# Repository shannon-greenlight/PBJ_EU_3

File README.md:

# The PBJ EU
The PBJ EU is a hardware development system for Eurorack synthesizers

Features:
- 800 point solderless proto board
- 4 switched 3.5mm jacks.
- Tip and Switch signals are routed from the jacks to the wiring connector.
- +/- 12V and adjustable A and B power rails are routed to the wiring connector.
- LED monitors for each jack. Red indicates positive voltage. Green indicates negative.
- 2 Test points per jack gives convenient access for probing and injecting signals.
- 2 Large Ground connection points are excellent for attaching alligator clips.
- 3 MULT switches connect jack 1 to 2, jack 2 to 3 or jack 3 to 4.
- Power is switched.
- Power indicators show the status of all power rails.
- 22 HP wide.
- Ready when you are. Everything you need with no pre-setup required!

# Making Changes
The process of making changes usually starts with altering the schematic followed by other actions as required.
This requires a properly configured KiCAD installation. Download the KiCAD [repo](https://github.com/shannon-greenlight/KiCAD) and follow the instructions in the README to install.
When the system is configured follow the steps outlined below. Some steps are optional depending on what has changed.

These procedures have been optimized for use with Digi-Key and JLCPCB. They should be a good starting point for use with other vendors.

- Update schematic
	- Update revision in File->Page Settings
	- Plot pdf version of schematic.
- If any parts have changed, Update BOMs
	- From KiCAD Schematic Editor, run Tools->Generate Legacy Bill of Materials using bom2grouped_csv.xsl
		- bom2grouped_csv.xsl is found in the Greenface KiCAD repo.
		- Here is a sample command line: xsltproc -o "%O.csv" "C:\Users\shann\Dropbox\KiCAD\bom2grouped_csv.xsl" "%I"
		- This creates a .csv and an xml file. The xml file is used in the next step.
	- Run _combine_boms.bat_
		- This creates the following .csv files
			- BOM\Digi-Key\PBJ_EU_combined.csv (all components, both boards combined)
			- BOM\Digi-Key\PBJ_EU_full.csv (all components, top board)
			- BOM\Digi-Key\PBJ_EU_split.csv (just components on top board that are not found in LCSC BOM)
			- BOM\LCSC\PBJ_EU_bom.csv (just components on top board to be assembled by JLCPCB)
			- sub\BOM\Digi-Key\PBJ_EU_full.csv (all components, sub board)
			- sub\BOM\Digi-Key\PBJ_EU_split.csv (just components on sub board that are not found in LCSC BOM)
			- sub\BOM\LCSC\PBJ_EU_bom.csv (just components on sub board to be assembled by JLCPCB)
		- combine_boms.bat requires Python and the Greenface Python [libraries](https://github.com/shannon-greenlight/PYTHON_BOM) to be installed
			- Place the Greenface Python folder in a convienient place on your computer and set the variable %plugin_dir% to point to that folder location.
			- Python is invoked as 'py' in the batch file. This may need to be changed depending on your Python installation.
- Update layout if required
	- Update revision in File->Page Settings
	- Plot the Gerber files
		- Set the output directory to _fab\gerber\\_
		- Make sure to Generate Drill Files
		- Create a zip archive of the Gerber files. (This is required by JLCPCB)
			- Use Windows Send To Compressed Folder. Rename the resulting file to PBJ_EU_gerbers.zip
			- Alternatively, use zip_gerbers.bat
			- zip_gerbers.bat requires 7z.exe
			- Edit this file if 7z.exe is installed somewhere other than C:\Program Files\7-Zip
	- Create the pick-and-place files
		- From KiCAD PCB Editor, run File->Fabrication Outputs->Component Placement
		- Set the output directory to _fab\pos\\_
		- This creates the files used by the next step
		- Update PBJ_EU_cpl.xlsx
			- PBJ_EU_cpl.xlsx uses Excel Queries to convert pos\PBJ_EU-top-pos.csv into a format compatible with JLCPCB
			- Excel requires an absolute path to the source folder of the data. Edit the query to enter the path to your project.
			- *note: This process does not produce a perfect placement file due to differences in how KiCAD and JLCPCB orient components. However, JLCPCB is able to use the file without problems. So, even if the placement looks wrong when specifying the build, they will use the file and produce correct boards.
			- **note: There is probably a KiCAD plugin available that does a better job. The user is encouraged to try this route and report the results back.
- Upload to JLCPCB
	- JLCPCB requires the following files:
		- fab\PBJ_EU_gerbers.zip
		- fab\PBJ_EU_cpl.xlsx (only needed for assembly)
		- bom\LCSC\PBJ_EU_bom.csv (only needed for assembly)

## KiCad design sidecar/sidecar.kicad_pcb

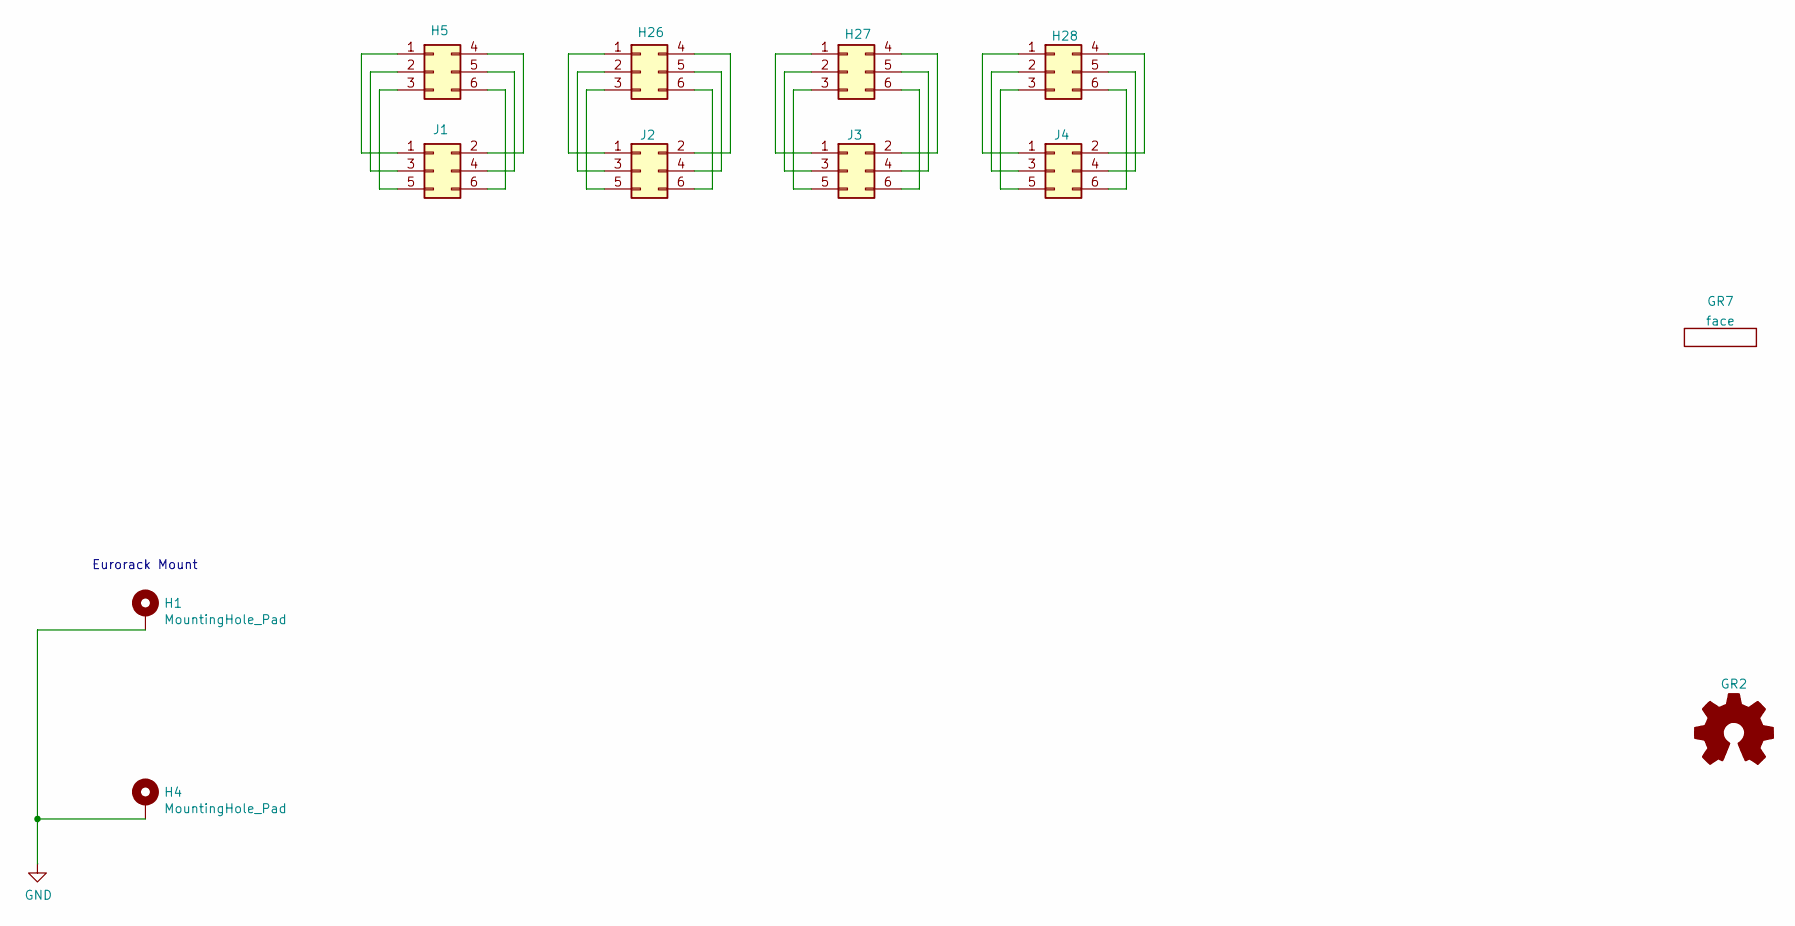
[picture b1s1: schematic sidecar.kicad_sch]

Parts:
GR2: Logo_Open_Hardware_Small; OSHW-Logo_5.7x6mm_SilkScreen
GR7: face; small_face
H1, H4: MountingHole_Pad; MountingHole_3.2mm_M3_Slot
H5: Adj 1; Potentiometer_Sidecar
H26: Adj 2; Potentiometer_Sidecar
H27: Adj 3; Potentiometer_Sidecar
H28: Adj 4; Potentiometer_Sidecar
J1, J2, J3, J4: Conn_02x03_Odd_Even; PinSocket_2x03_P2.54mm_Vertical; Digi-Key Part S7071-ND

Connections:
GND: H1.1, H4.1
unnamed: H5.1, J1.1
unnamed: H5.2, J1.3
unnamed: H5.3, J1.5
unnamed: H5.4, J1.2
unnamed: H5.5, J1.4
unnamed: H5.6, J1.6
unnamed: H26.1, J2.1
unnamed: H26.2, J2.3
unnamed: H26.3, J2.5
unnamed: H26.4, J2.2
unnamed: H26.5, J2.4
unnamed: H26.6, J2.6
unnamed: H27.1, J3.1
unnamed: H27.2, J3.3
unnamed: H27.3, J3.5
unnamed: H27.4, J3.2
unnamed: H27.5, J3.4
unnamed: H27.6, J3.6
unnamed: H28.1, J4.1
unnamed: H28.2, J4.3
unnamed: H28.3, J4.5
unnamed: H28.4, J4.2
unnamed: H28.5, J4.4
unnamed: H28.6, J4.6

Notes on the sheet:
Eurorack Mount

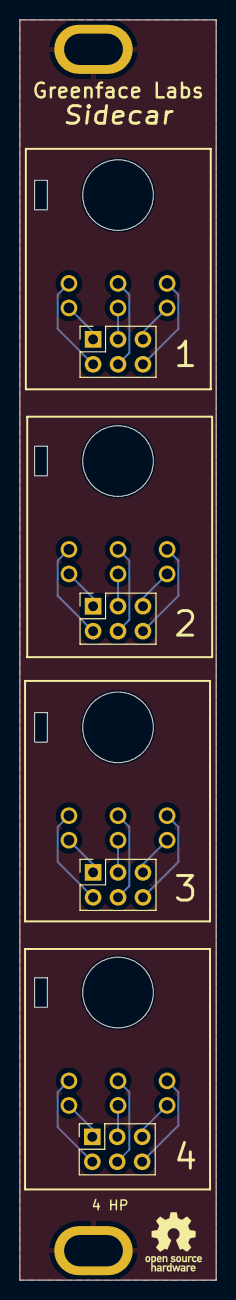
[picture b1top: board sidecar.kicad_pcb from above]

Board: 2 copper layers, 20.0 x 128.4 mm, 11 parts (0 on the bottom side), 25 nets.

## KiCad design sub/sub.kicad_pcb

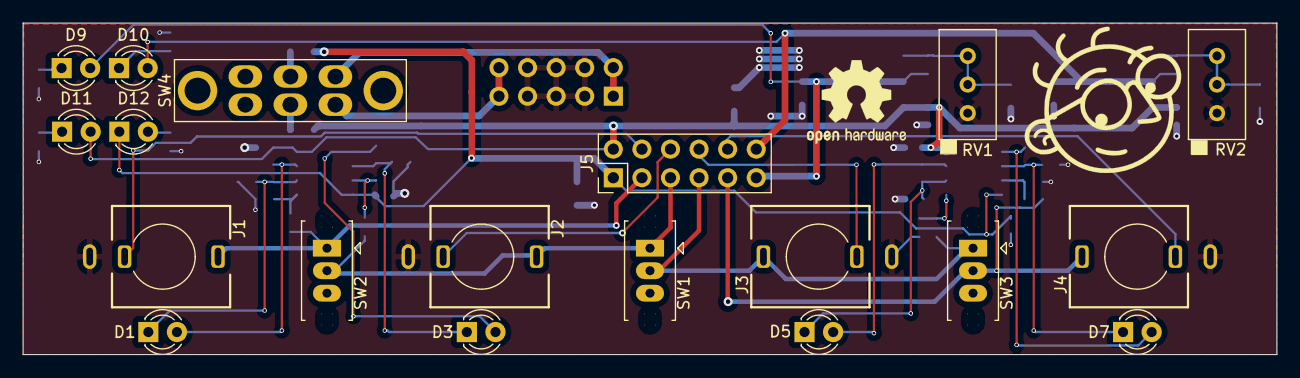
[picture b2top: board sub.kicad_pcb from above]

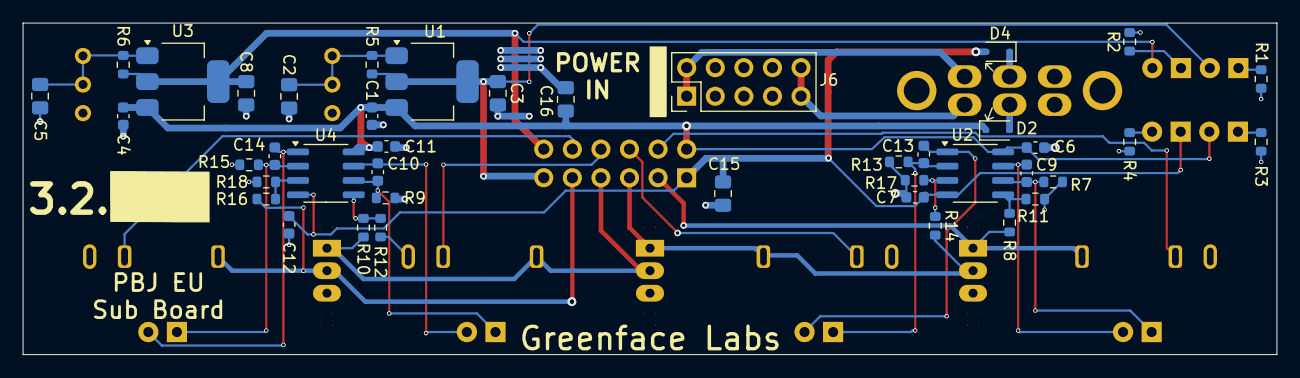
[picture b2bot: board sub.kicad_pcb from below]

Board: 2 copper layers, 111.4 x 29.4 mm, 62 parts (41 on the bottom side), 35 nets.

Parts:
C1, C4, C6, C7, C11, C12: 100nF; C_0603_1608Metric
C2, C5: 10uF; C_0805_2012Metric_Pad1.18x1.45mm_HandSolder
C3, C8, C15, C16: 22uF; C_0805_2012Metric_Pad1.18x1.45mm_HandSolder
C9, C10, C13, C14: 10nF; C_0603_1608Metric
D1, D3, D5, D7: LED_RG; LED_D3.0mm
D2, D4: 1N5819WS; D_SOD-323
D9: GREEN LED; LED_D3.0mm
D10: YELLOW LED; LED_D3.0mm
D11: RED LED; LED_D3.0mm
D12: BLUE LED; LED_D3.0mm
GR1: small_logo; small_face
GR2: OSWF_logo; OSHW-Logo2_9.8x8mm_SilkScreen
J1, J2, J3, J4: Thonk 3.5mm Jack; Jack_3.5mm_QingPu_WQP-PJ398SM_Vertical
J5: Conn_02x06_Odd_Even; PinHeader_2x06_P2.54mm_Vertical
J6: Conn_02x05_Odd_Even; PinHeader_2x05_P2.54mm_Vertical
R1, R2, R5, R6: 620; R_0603_1608Metric
R3, R4: 2.2K; R_0603_1608Metric
R7, R9, R13, R15: 510; R_0603_1608Metric
R8, R10, R11, R12, R14, R16, R17, R18: 1M; R_0603_1608Metric
RV1, RV2: 5K; Potentiometer_Bourns_3296W_Vertical
SW1, SW2, SW3: SW_SPDT; SW_Slide_EG1248
SW4: MFS201N-9-Z; MFS201N−9−Z
U1, U3: LM317; SOT-223-3_TabPin2
U2, U4: TL072CDR; SOIC-8_3.9x4.9mm_P1.27mm

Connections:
+12V: C1.1, C4.1, C6.1, C11.1, C16.2, D2.1 (K), D11.2 (A), J5.2, U1.3 (VI), U2.8 (V+), U3.3 (VI), U4.8 (V+)
-12V: C7.2, C12.2, C15.1, D4.2 (A), D12.1 (K), J5.1, U2.4 (V-), U4.4 (V-)
A Rail: C3.1, D9.2 (A), J5.11, R5.1, U1.2 (VO)
B Rail: C8.1, D10.2 (A), J5.12, R6.1, U3.2 (VO)
GND: C1.2, C2.2, C3.2, C4.2, C5.2, C6.2, C7.1, C8.2, C11.2, C12.1, C15.2, C16.1, J1.S, J2.S, J3.S, J4.S, J6.3, J6.4, J6.5, J6.6, J6.7, J6.8, R1.1, R2.2, R3.2, R4.2, R7.1, R9.1, R11.2, R12.2, R13.1, R15.1, R17.2, R18.2, RV1.1, RV2.1
unnamed: C9.2, D1.2 (AK), U2.7
unnamed: C9.1, D1.1 (KA), R7.2, U2.6 (-)
unnamed: D2.2 (A), SW4.5 (B)
unnamed: C13.2, D3.2 (AK), U2.1
unnamed: C13.1, D3.1 (KA), R13.2, U2.2 (-)
unnamed: D4.1 (K), SW4.2 (B)
unnamed: C10.2, D5.2 (AK), U4.7
unnamed: C10.1, D5.1 (KA), R9.2, U4.6 (-)
unnamed: C14.2, D7.2 (AK), U4.1
unnamed: C14.1, D7.1 (KA), R15.2, U4.2 (-)
unnamed: D9.1 (K), R1.2
unnamed: D10.1 (K), R2.1
unnamed: D11.1 (K), R3.1
unnamed: D12.2 (A), R4.1
unnamed: J6.1, J6.2, SW4.3 (C)
unnamed: J6.9, J6.10, SW4.6 (C)
unnamed: C2.1, R5.2, RV1.2, RV1.3, U1.1 (ADJ)
unnamed: R14.1, R17.1, U2.3 (+)
unnamed: R8.1, R11.1, U2.5 (+)
unnamed: C5.1, R6.2, RV2.2, RV2.3, U3.1 (ADJ)
unnamed: R16.1, R18.1, U4.3 (+)
unnamed: R10.1, R12.1, U4.5 (+)
SW1: J1.TN, J5.4
SW2: J2.TN, J5.6
SW3: J3.TN, J5.8
SW4: J4.TN, J5.10
Tip1: J1.T, J5.3, R8.2, SW2.1 (A)
Tip2: J2.T, J5.5, R14.2, SW1.1 (A), SW2.2 (B)
Tip3: J3.T, J5.7, R10.2, SW1.2 (B), SW3.1 (A)
Tip4: J4.T, J5.9, R16.2, SW3.2 (B)

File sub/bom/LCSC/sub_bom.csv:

"Designator","Comment","Footprint","JLCPCBPart#"
"C1, C4, C6, C7, C11, C12, ","100nF","Capacitor_SMD:C_0603_1608Metric","C14663"
"C2, C5, ","10uF","Capacitor_SMD:C_0805_2012Metric_Pad1.18x1.45mm_HandSolder","C15850"
"C3, C8, ","22uF","Capacitor_SMD:C_0805_2012Metric_Pad1.18x1.45mm_HandSolder","C76637"
"C9, C10, C13, C14, ","10nF","Capacitor_SMD:C_0603_1608Metric","C1589"
"J6, ","Conn_02x05_Odd_Even","Connector_PinHeader_2.54mm:PinHeader_2x05_P2.54mm_Vertical","C492422"
"R1, R2, R5, R6, ","620","Resistor_SMD:R_0603_1608Metric","C23220"
"R3, R4, ","2.2K","Resistor_SMD:R_0603_1608Metric","C4190"
"R7, R9, R13, R15, ","510","Resistor_SMD:R_0603_1608Metric","C23193"
"R8, R10, R11, R12, R14, R16, R17, R18, ","1M","Resistor_SMD:R_0603_1608Metric","C22935"
"U1, U3, ","LM317","Package_TO_SOT_SMD:SOT-223-3_TabPin2","C51466"
"U2, U4, ","TL072CDR","Package_SO:SOIC-8_3.9x4.9mm_P1.27mm","C6961"

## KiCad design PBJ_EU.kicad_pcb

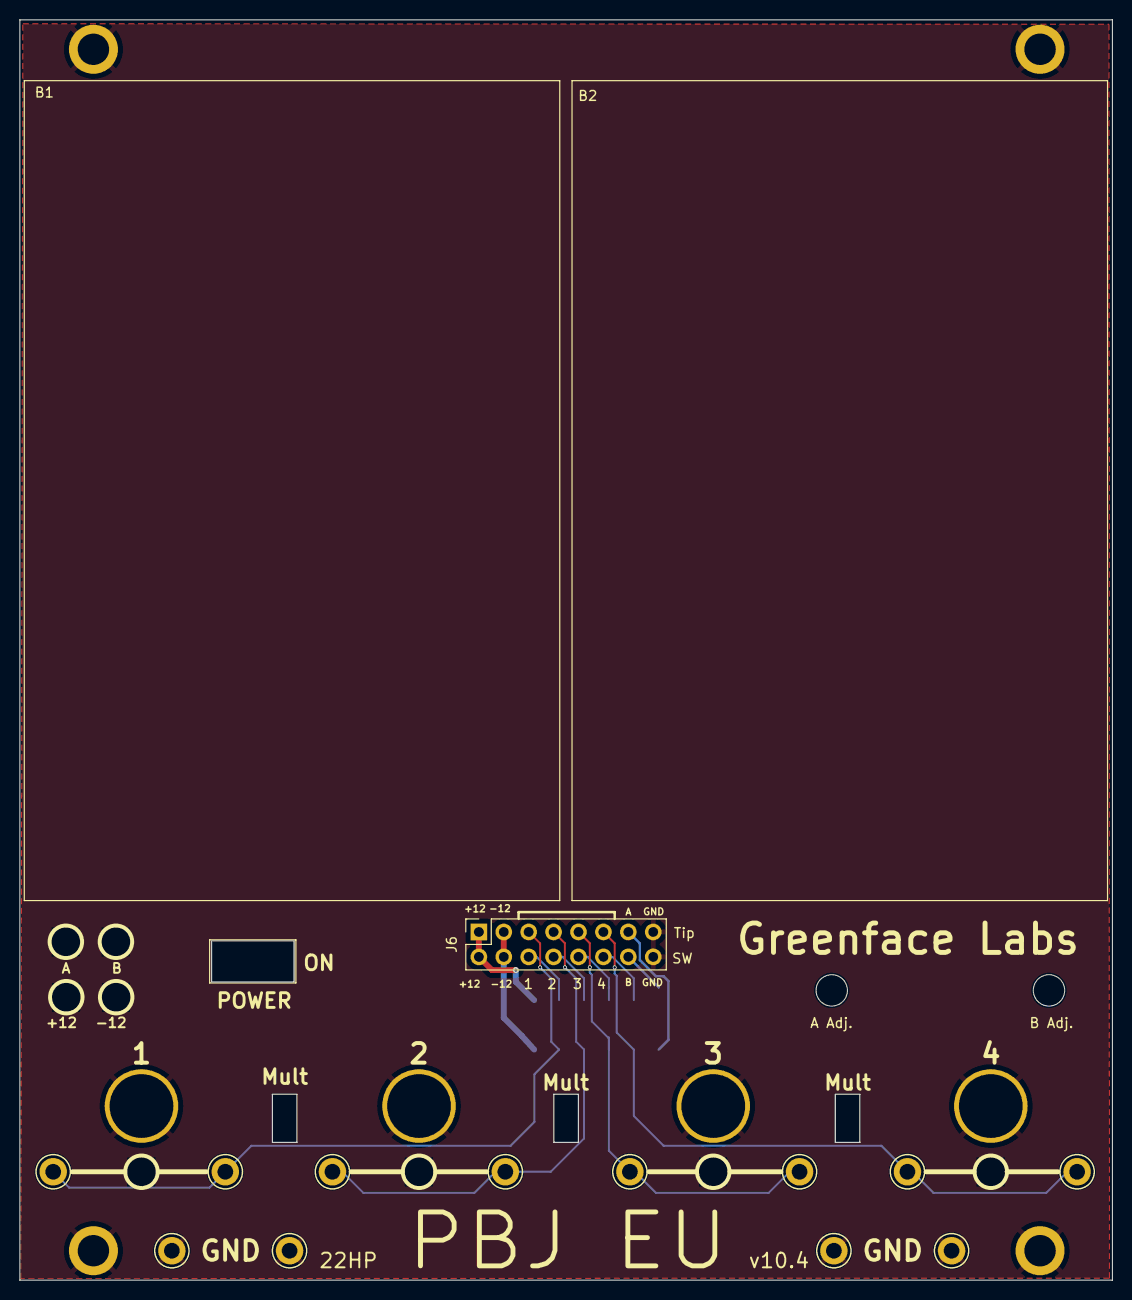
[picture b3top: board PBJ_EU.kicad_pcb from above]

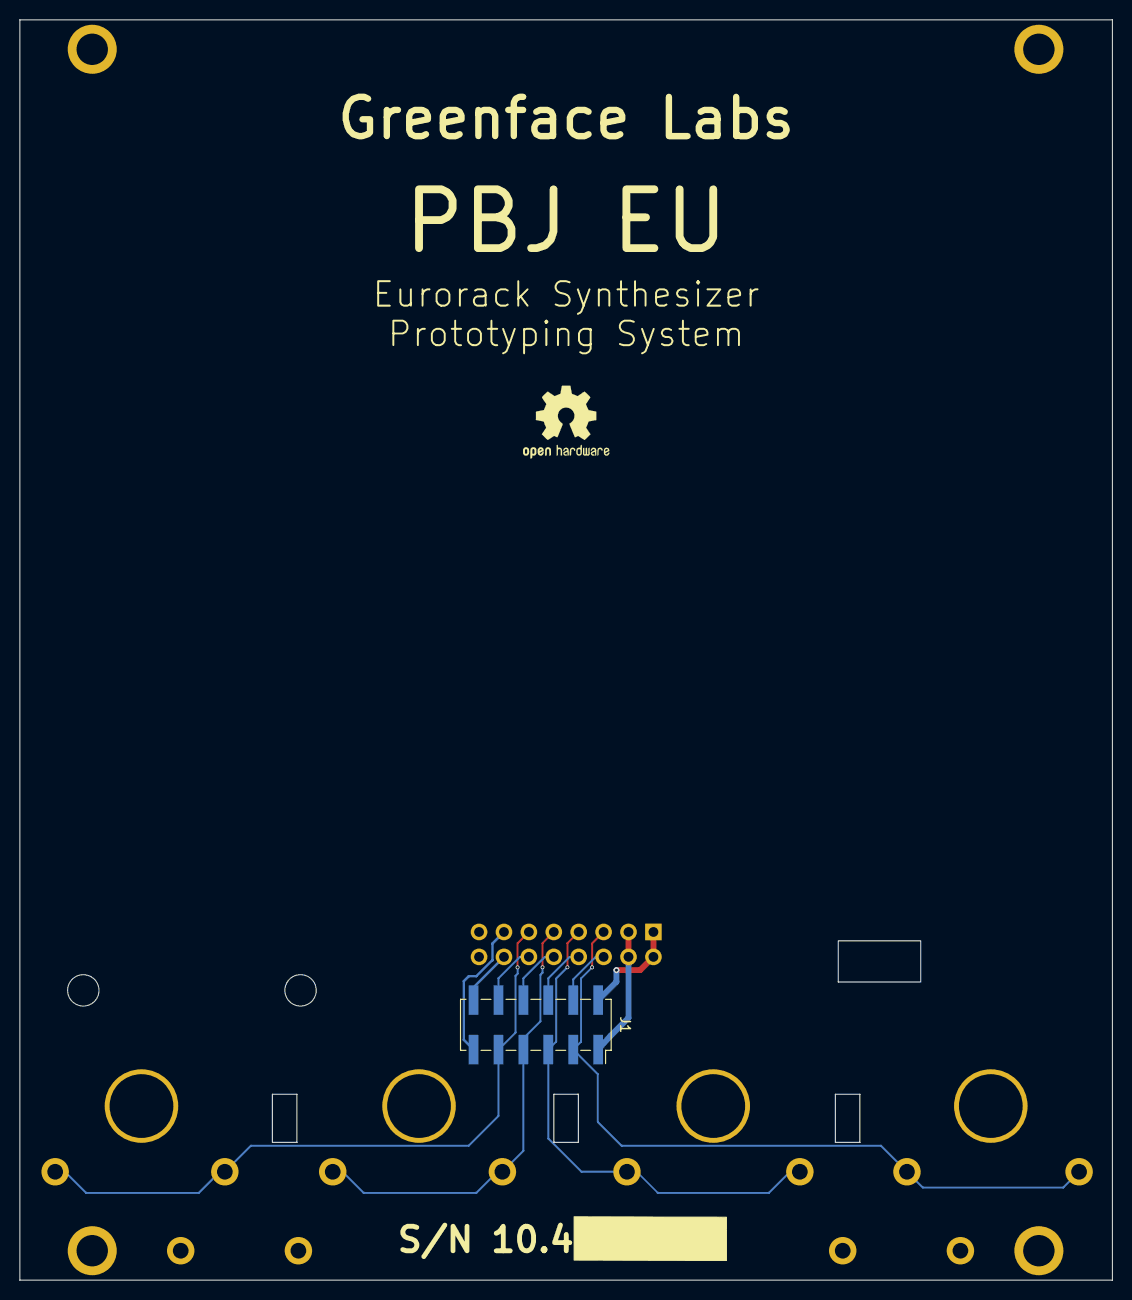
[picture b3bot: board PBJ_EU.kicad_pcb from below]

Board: 2 copper layers, 111.3 x 128.4 mm, 39 parts (2 on the bottom side), 13 nets.

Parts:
B1, B2: Breadboard_400; Proto_400
GR2: OSWF_logo; OSHW-Logo2_9.8x8mm_SilkScreen
H1, H2, H3, H4: MountingHole_Pad; MountingHole_3.2mm_M3_SmPad
H5, H6, H7, H8: MountingHole_Pad; Jack_3.5mm_QingPu_WQP-PJ398SM_Vertical
H9, H10: MountingHole; MountingHole_3.2mm_M3
J1: Conn_02x06_Odd_Even; PinSocket_2x06_P2.54mm_Vertical_SMD_no_holes
J6: Conn_02x08_Odd_Even_Female; PinSocket_2x08_P2.54mm_Vertical
LED1, LED2, LED3, LED4: Red/Green Led; 3mmLED_seethru_small
LED9: Grn Led; 3mmLED_seethru_small
LED10: Yel Led; 3mmLED_seethru_small
LED11: Red Led; 3mmLED_seethru_small
LED12: Blue Led; 3mmLED_seethru_small
MULT1, MULT2, MULT3: Mult; EG1248
SW3: Power; MFS201N−9−Z
TP1, TP2, TP3, TP4, TP5, TP6, TP7, TP8, TP9, TP10, TP11, TP12: TestPoint; TestPoint_Keystone_5005-5009_Compact

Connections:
+12V: J1.2, J6.1, J6.2
-12V: J1.1, J6.3, J6.4
A Rail: J1.11, J6.13
B Rail: J1.12, J6.14
GND: H1.1, H2.1, H3.1, H4.1, H5.1, H6.1, H7.1, H8.1, J6.15, J6.16, TP9.1, TP10.1, TP11.1, TP12.1
SW1: J1.4, J6.6
SW2: J1.6, J6.8
SW3: J1.8, J6.10
SW4: J1.10, J6.12
Tip1: J1.3, J6.5, TP1.1, TP2.1
Tip2: J1.5, J6.7, TP5.1, TP6.1
Tip3: J1.7, J6.9, TP3.1, TP4.1
Tip4: J1.9, J6.11, TP7.1, TP8.1

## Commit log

2025-02-09 Init checkin
2025-02-14 v3.2
2025-02-14 Removes temp files.
2025-02-14 Adds mention of GND bar.
2025-07-24 v 10.4
2025-07-24 Removes Other from BOMS
2025-08-04 Adds Sidecar v0.1
